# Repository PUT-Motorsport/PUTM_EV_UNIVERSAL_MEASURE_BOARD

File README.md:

# Universal Measurement Board v2.0

---

# Changes

Revision 2.0 has the same functionality as v1.1 but has been reduced in size to meet the 10×10 cm production constraints required by the manufacturer.

# Description

UMB (Universal Measurement Board) is a project designed as multi-channel analog input device to allow various types of electrical measurements.
It provides 8 channels that can be used either as differential or single-ended measurement inputs. All signals are routed through an analog multiplexer, a programmable gain amplifier and an external ADC. Measurements are acquired by a microcontroller and transmitted via an FDCAN interface to a host device for further processing.

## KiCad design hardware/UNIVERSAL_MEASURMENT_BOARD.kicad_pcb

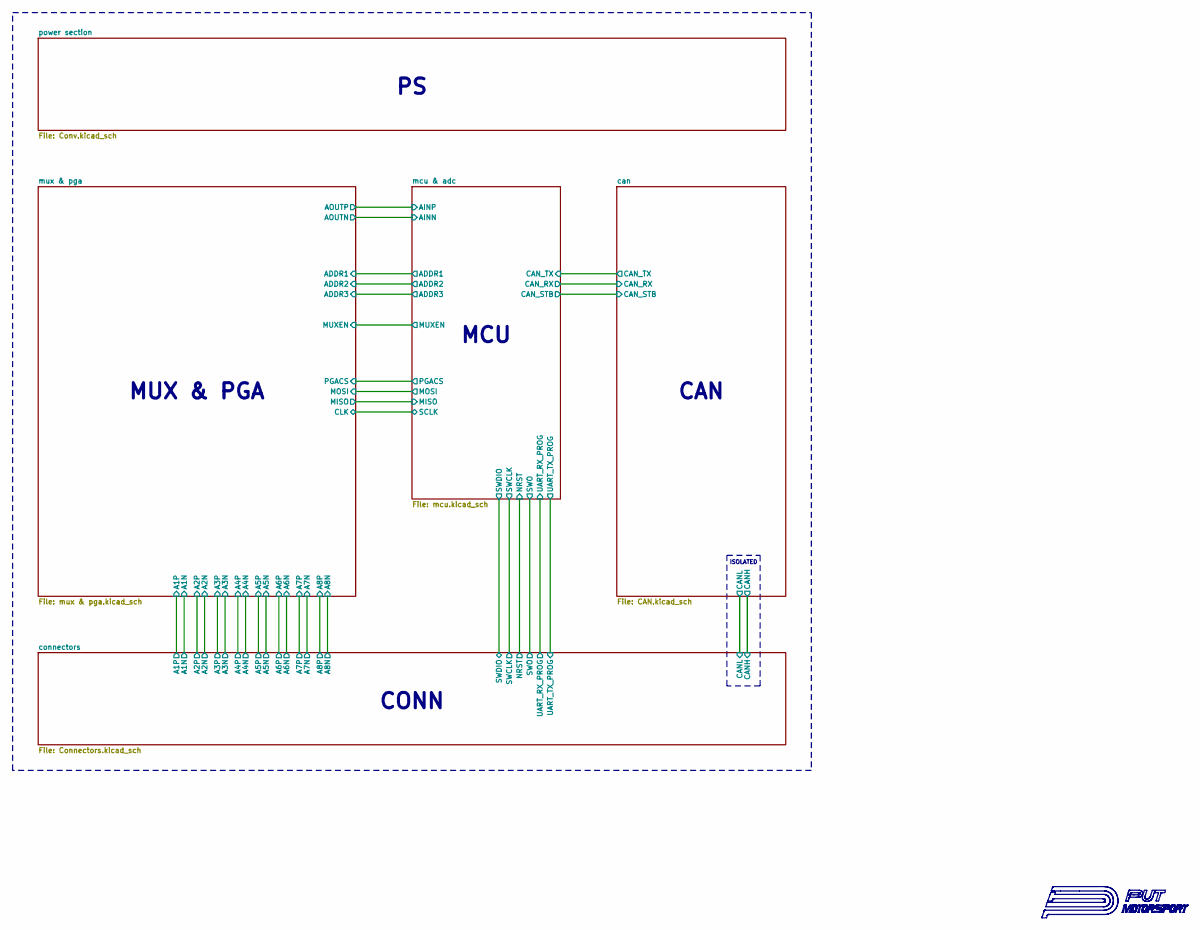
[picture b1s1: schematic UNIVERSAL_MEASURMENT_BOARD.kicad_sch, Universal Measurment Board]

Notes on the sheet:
CAN
CONN
MUX & PGA
MCU
ISOLATED

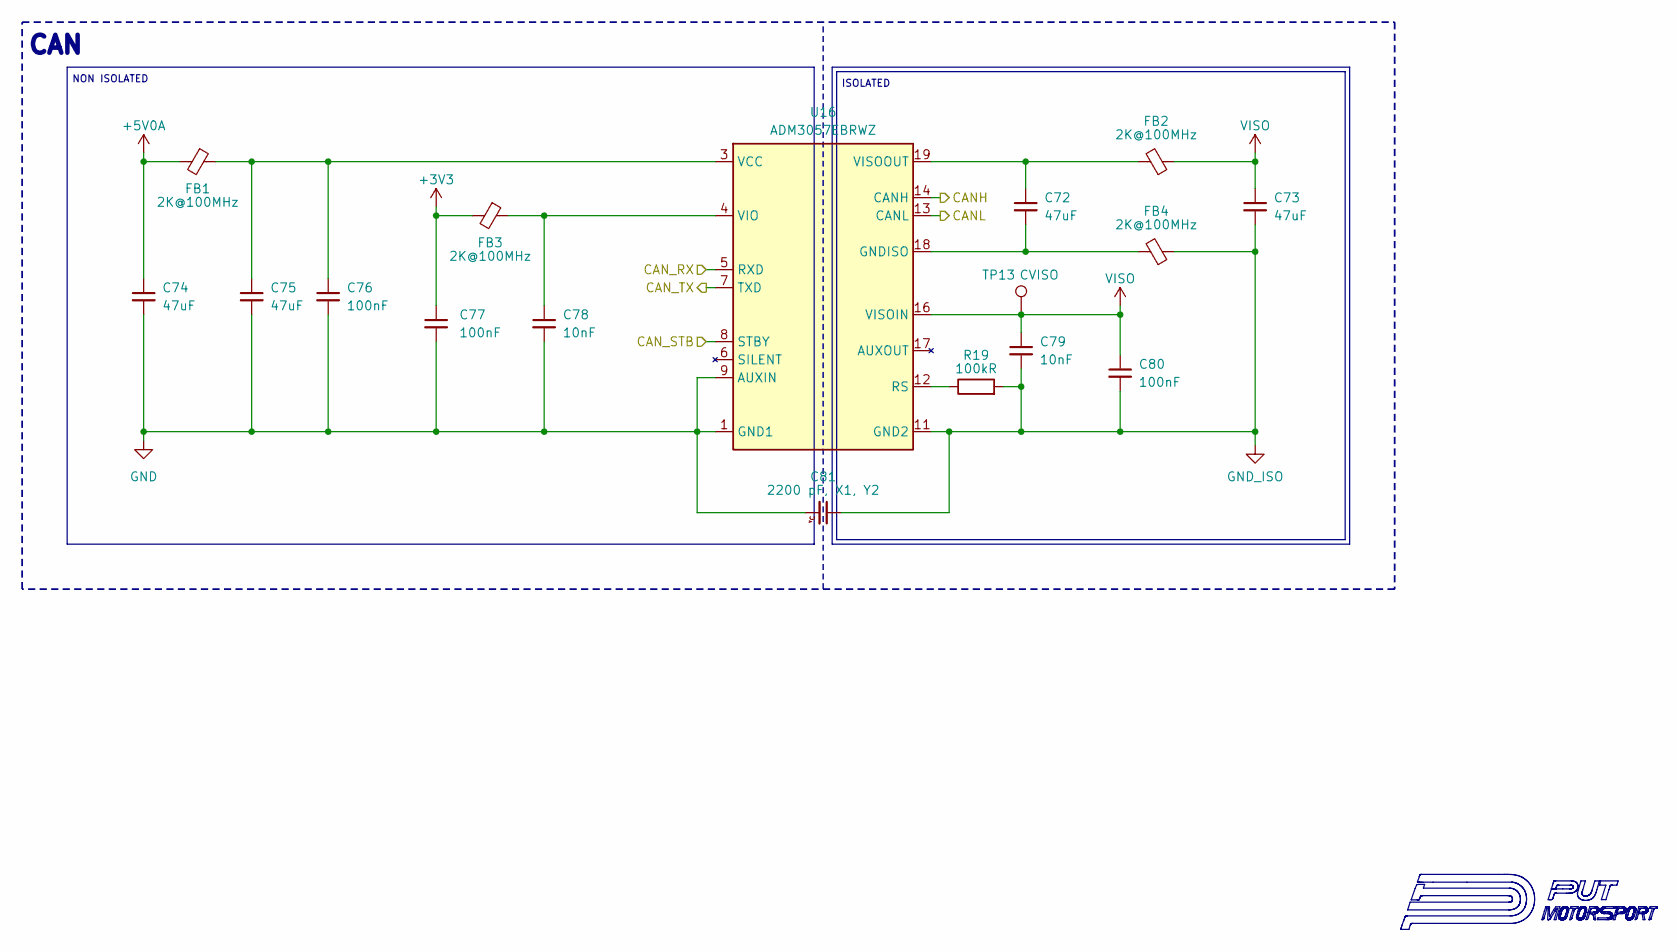
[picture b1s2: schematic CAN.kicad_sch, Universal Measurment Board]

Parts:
C72, C73, C74, C75: 47uF; C_0603_1608Metric
C76, C77, C80: 100nF; C_0603_1608Metric
C78, C79: 10nF; C_0603_1608Metric
C81: 2200 pF, X1, Y2; CAPC5728X280N; Mouser Part Number 791-S252B222K502CT
FB1, FB2, FB3, FB4: 2K@100MHz; L_0805_2012Metric
R19: 100kR; R_0603_1608Metric
TP13: CVISO; TestPoint_Pad_D1.5mm
U16: ADM3057EBRWZ; SOIC127P1032X265-20N; Mouser Part Number 584-ADM3057EBRWZ

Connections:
+3V3: C77.1, FB3.2; also elsewhere on the board
+5V0A: C74.1, FB1.2; also elsewhere on the board
/can/CANH: U16.14 (CANH); also elsewhere on the board
/can/CANL: U16.13 (CANL); also elsewhere on the board
/can/CAN_RX: U16.5 (RXD); also elsewhere on the board
/can/CAN_STB: U16.8 (STBY); also elsewhere on the board
/can/CAN_TX: U16.7 (TXD); also elsewhere on the board
GND: C74.2, C75.2, C76.2, C77.2, C78.2, C81.2, U16.1 (GND1), U16.2 (GND1_2), U16.9 (AUXIN), U16.10 (GND1_3); also elsewhere on the board
GND_ISO: C73.2, C79.2, C80.2, C81.1, FB4.1, R19.2, U16.11 (GND2), U16.15 (GND2_2); also elsewhere on the board
unnamed: C72.2, FB4.2, U16.18 (GNDISO), U16.20 (GNDISO_2)
unnamed: R19.1, U16.12 (RS)
unnamed: C75.1, C76.1, FB1.1, U16.3 (VCC)
unnamed: C78.1, FB3.1, U16.4 (VIO)
unnamed: C72.1, FB2.2, U16.19 (VISOOUT)
VISO: C73.1, C79.1, C80.1, FB2.1, TP13.1, U16.16 (VISOIN)

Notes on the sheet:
CAN
ISOLATED
NON ISOLATED

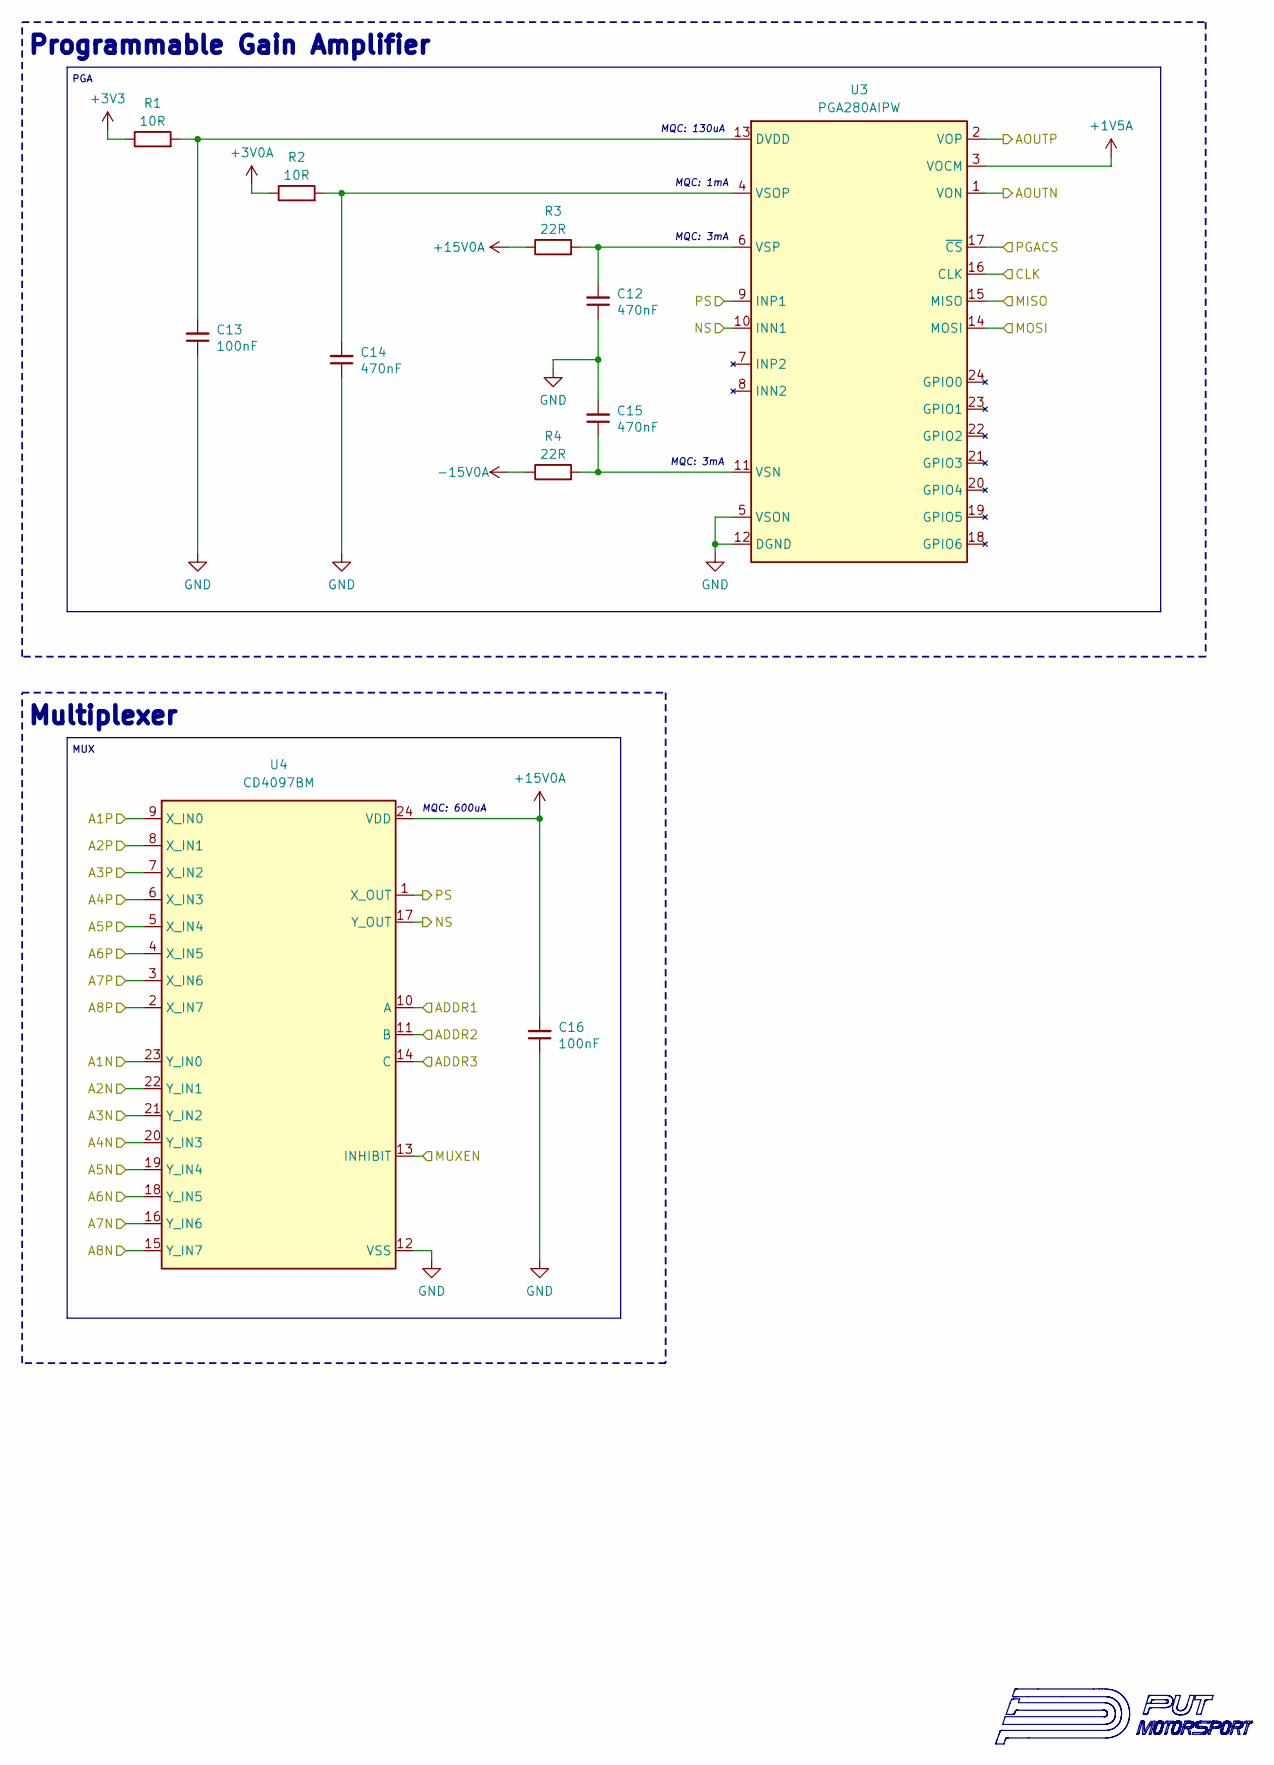
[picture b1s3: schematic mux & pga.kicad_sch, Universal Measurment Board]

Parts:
C12, C14, C15: 470nF; C_0603_1608Metric; Manufacturer_Part_Number CL21A107MQYNNWE; Mouser Part Number 810-C2012X5R1V226MAC
C13, C16: 100nF; C_0603_1608Metric; Manufacturer_Part_Number CL21A107MQYNNWE; Mouser Part Number 810-C2012X5R1V226MAC
R1, R2: 10R; R_0603_1608Metric
R3, R4: 22R; R_0603_1608Metric
U3: PGA280AIPW; SOP65P640X120-24N; Mouser Part Number 595-PGA280AIPW
U4: CD4097BM; SOIC127P1030X265-24N; Mouser Part Number 595-CD4097BM

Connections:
+1V5A: U3.3 (VOCM); also elsewhere on the board
+3V0A: R2.1; also elsewhere on the board
+3V3: R1.1; also elsewhere on the board
+15V0A: C16.2, R3.1, U4.24 (VDD); also elsewhere on the board
-15V0A: R4.1; also elsewhere on the board
/connectors/A1N: U4.23 (Y_IN0); also elsewhere on the board
/connectors/A1P: U4.9 (X_IN0); also elsewhere on the board
/connectors/A2N: U4.22 (Y_IN1); also elsewhere on the board
/connectors/A2P: U4.8 (X_IN1); also elsewhere on the board
/connectors/A3N: U4.21 (Y_IN2); also elsewhere on the board
/connectors/A3P: U4.7 (X_IN2); also elsewhere on the board
/connectors/A4N: U4.20 (Y_IN3); also elsewhere on the board
/connectors/A4P: U4.6 (X_IN3); also elsewhere on the board
/connectors/A5N: U4.19 (Y_IN4); also elsewhere on the board
/connectors/A5P: U4.5 (X_IN4); also elsewhere on the board
/connectors/A6N: U4.18 (Y_IN5); also elsewhere on the board
/connectors/A6P: U4.4 (X_IN5); also elsewhere on the board
/connectors/A7N: U4.16 (Y_IN6); also elsewhere on the board
/connectors/A7P: U4.3 (X_IN6); also elsewhere on the board
/connectors/A8N: U4.15 (Y_IN7); also elsewhere on the board
/connectors/A8P: U4.2 (X_IN7); also elsewhere on the board
/mcu & adc/ADDR1: U4.10 (A); also elsewhere on the board
/mcu & adc/ADDR2: U4.11 (B); also elsewhere on the board
/mcu & adc/ADDR3: U4.14 (C); also elsewhere on the board
/mcu & adc/AINN: U3.1 (VON); also elsewhere on the board
/mcu & adc/AINP: U3.2 (VOP); also elsewhere on the board
/mcu & adc/MISO: U3.15 (MISO); also elsewhere on the board
/mcu & adc/MOSI: U3.14 (MOSI); also elsewhere on the board
/mcu & adc/MUXEN: U4.13 (INHIBIT); also elsewhere on the board
/mcu & adc/PGACS: U3.17 (~CS); also elsewhere on the board
/mcu & adc/SCLK: U3.16 (CLK); also elsewhere on the board
/mux & pga/NS: U3.10 (INN1), U4.17 (Y_OUT)
/mux & pga/PS: U3.9 (INP1), U4.1 (X_OUT)
GND: C12.1, C13.1, C14.1, C15.2, C16.1, U3.5 (VSON), U3.12 (DGND), U4.12 (VSS); also elsewhere on the board
unnamed: C13.2, R1.2, U3.13 (DVDD)
unnamed: C15.1, R4.2, U3.11 (VSN)
unnamed: C14.2, R2.2, U3.4 (VSOP)
unnamed: C12.2, R3.2, U3.6 (VSP)

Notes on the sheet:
MQC: 130uA
Multiplexer
MQC: 1mA
PGA
Programmable Gain Amplifier
MQC: 600uA
MQC: 3mA
MUX

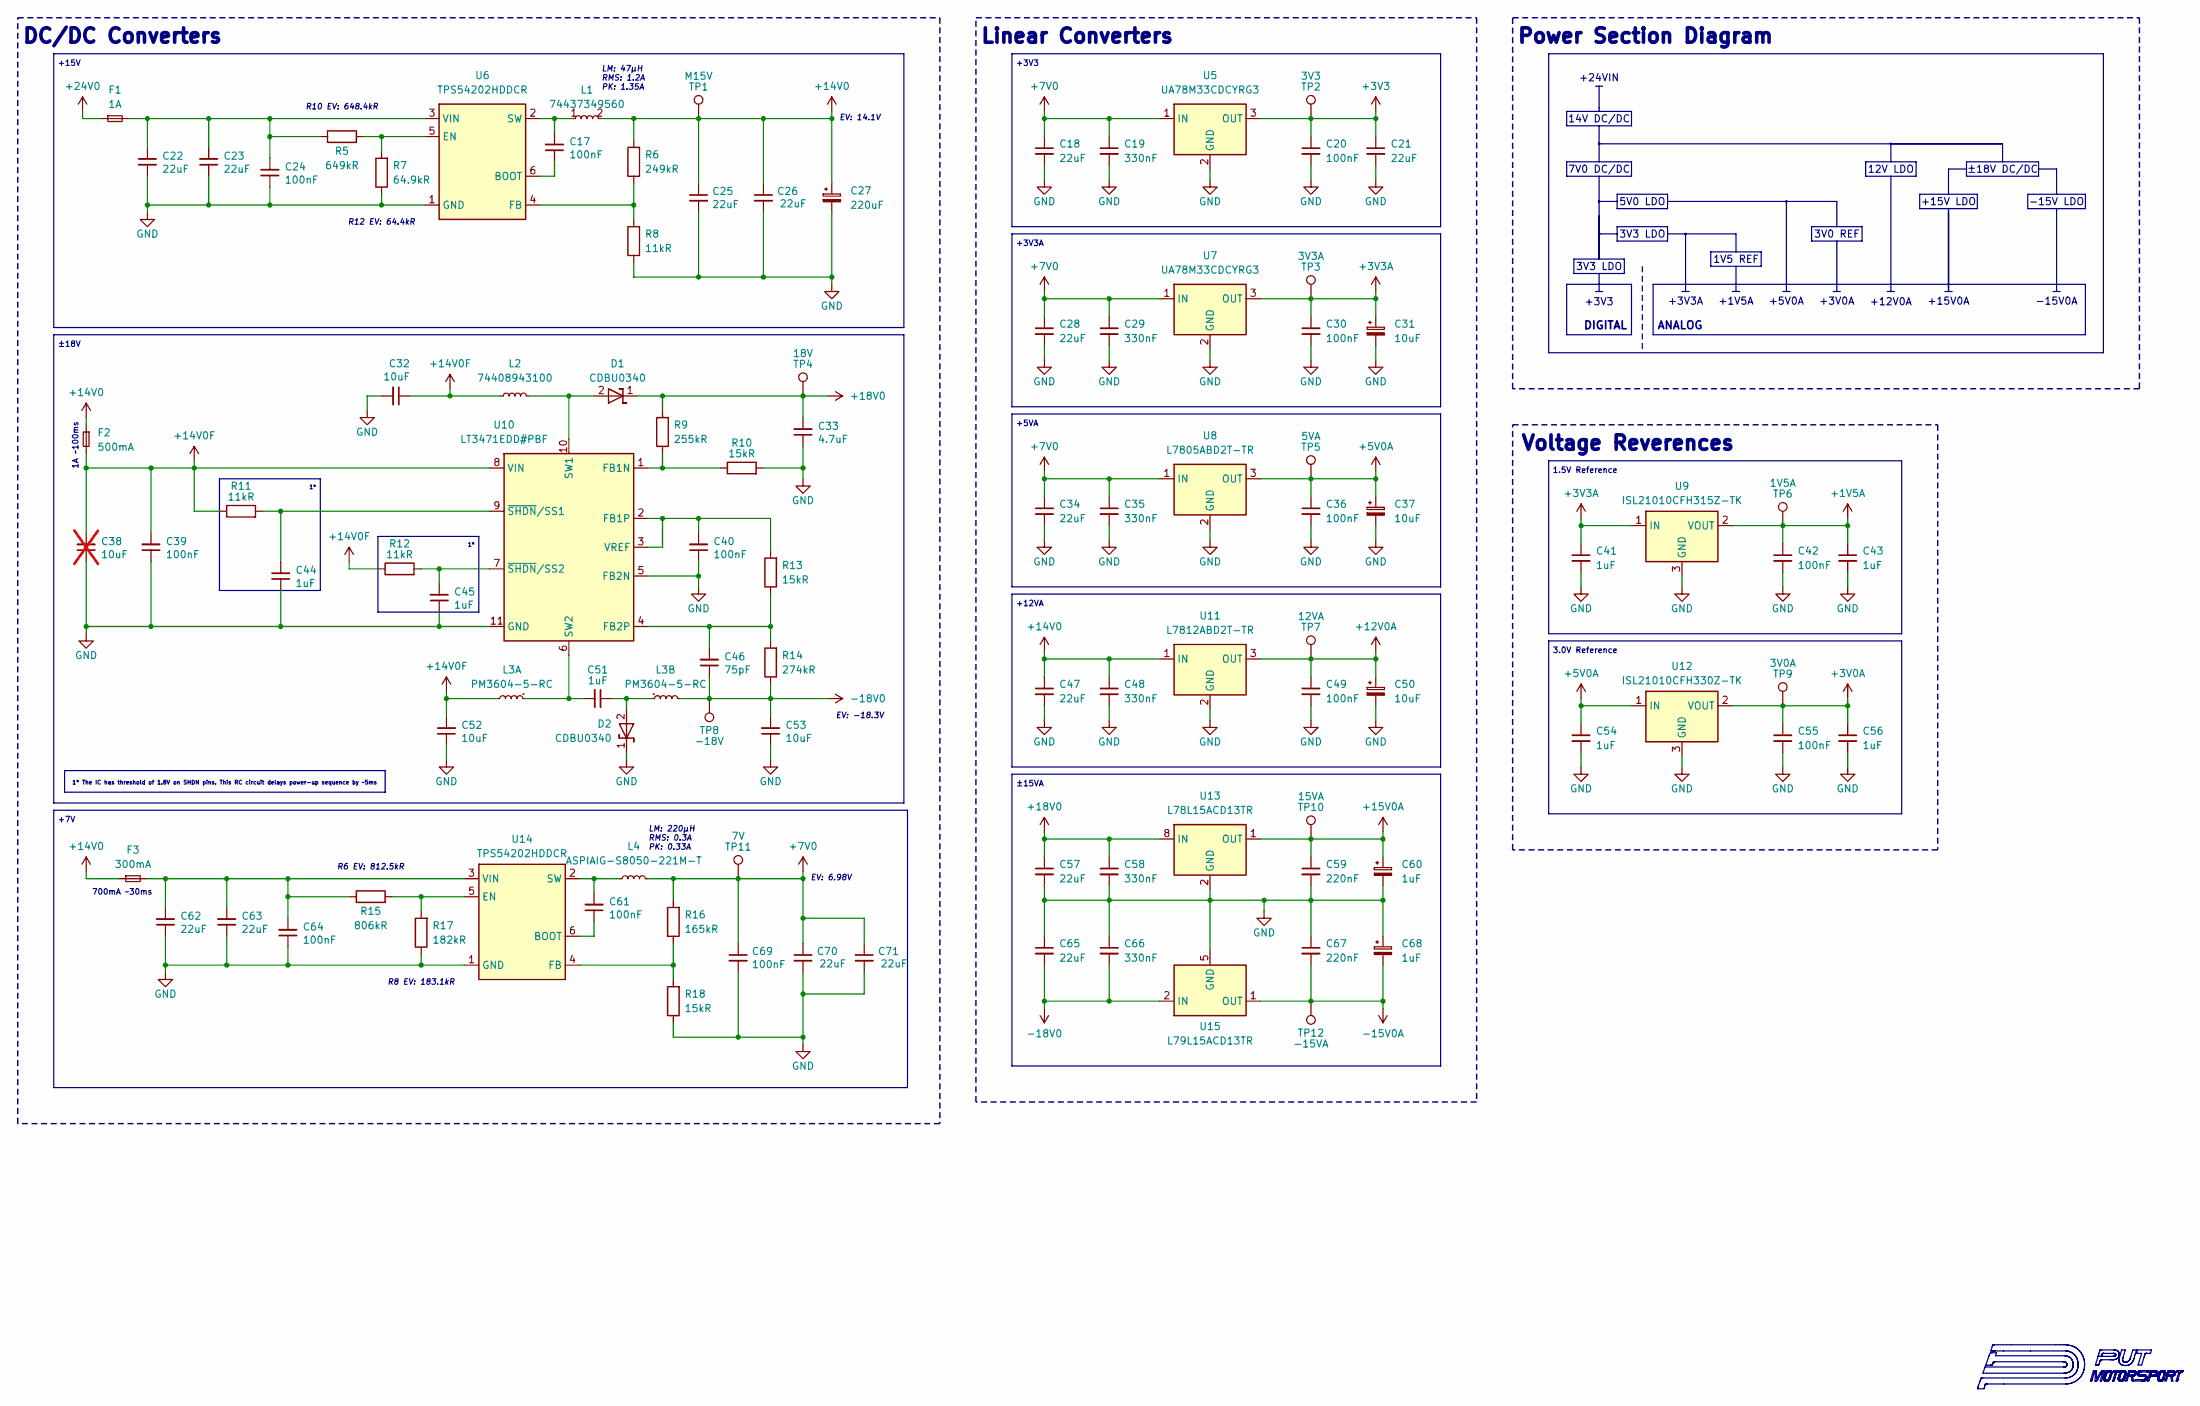
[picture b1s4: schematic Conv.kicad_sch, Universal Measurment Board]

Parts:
C17, C24, C61, C64: 100nF; C_0603_1608Metric; Manufacturer_Part_Number C0603C104J3RACTU; Mouser Part Number --
C18, C21, C28, C34, C47, C57, C62, C63, C65, C70, C71: 22uF; C_0603_1608Metric; Manufacturer_Part_Number CL21A107MQYNNWE; Mouser Part Number 810-C2012X5R1V226MAC
C19, C29, C35, C48, C58, C66: 330nF; C_0603_1608Metric; Manufacturer_Part_Number CL21A107MQYNNWE; Mouser Part Number 810-C2012X5R1V226MAC
C20, C30, C36, C39, C40, C42, C49, C55, C69: 100nF; C_0603_1608Metric; Manufacturer_Part_Number CL21A107MQYNNWE; Mouser Part Number 810-C2012X5R1V226MAC
C22, C23, C25, C26: 22uF; C_0805_2012Metric; Manufacturer_Part_Number CL21A107MQYNNWE; Mouser Part Number 810-C2012X5R1V226MAC
C27: 220uF; CP_Elec_8x10
C31, C37, C50: 10uF; CP_Elec_4x5.8
C32, C52, C53: 10uF; C_0805_2012Metric; Manufacturer_Part_Number CL21A107MQYNNWE; Mouser Part Number 810-C2012X5R1V226MAC
C33: 4.7uF; C_0805_2012Metric; Manufacturer_Part_Number CL21A107MQYNNWE; Mouser Part Number 810-C2012X5R1V226MAC
C38: 10uF; C_0805_2012Metric; Manufacturer_Part_Number CL21A107MQYNNWE; Mouser Part Number 810-C2012X5R1V226MAC; not fitted
C41, C43, C44, C45, C54, C56: 1uF; C_0603_1608Metric; Manufacturer_Part_Number CL21A107MQYNNWE; Mouser Part Number 810-C2012X5R1V226MAC
C46: 75pF; C_0603_1608Metric; Manufacturer_Part_Number CL21A107MQYNNWE; Mouser Part Number 810-C2012X5R1V226MAC
C51: 1uF; C_0805_2012Metric; Manufacturer_Part_Number CL21A107MQYNNWE; Mouser Part Number 810-C2012X5R1V226MAC
C59, C67: 220nF; C_0603_1608Metric; Manufacturer_Part_Number CL21A107MQYNNWE; Mouser Part Number 810-C2012X5R1V226MAC
C60, C68: 1uF; CP_Elec_4x5.4
D1, D2: CDBU0340; D_0603_1608Metric; Mouser Part Number 750-CDBU0340
F1: 1A; F_0805_2012Metric
F2: 500mA; F_0603_1608Metric
F3: 300mA; F_0603_1608Metric
L1: 74437349560; Mouser Part Number 710-74437349560
L2: 74408943100; WE-SPC_48XX78; Mouser Part Number 710-74408943100
L3: PM3604-5-RC; Mouser Part Number 710-74408943100
L4: ASPIAIG-S8050-221M-T; INDPM8080X520N; Mouser Part Number 815-ASPIAIGS8050221T
R5: 649kR; R_0603_1608Metric
R6: 249kR; R_0603_1608Metric
R7: 64.9kR; R_0603_1608Metric
R8, R11, R12: 11kR; R_0603_1608Metric
R9: 255kR; R_0603_1608Metric
R10, R13, R18: 15kR; R_0603_1608Metric
R14: 274kR; R_0603_1608Metric
R15: 806kR; R_0603_1608Metric
R16: 165kR; R_0603_1608Metric
R17: 182kR; R_0603_1608Metric
TP1: M15V; TestPoint_Pad_D1.5mm
TP2: 3V3; TestPoint_Pad_D1.5mm
TP3: 3V3A; TestPoint_Pad_D1.5mm
TP4: 18V; TestPoint_Pad_D1.5mm
TP5: 5VA; TestPoint_Pad_D1.5mm
TP6: 1V5A; TestPoint_Pad_D1.5mm
TP7: 12VA; TestPoint_Pad_D1.5mm
TP8: -18V; TestPoint_Pad_D1.5mm
TP9: 3V0A; TestPoint_Pad_D1.5mm
TP10: 15VA; TestPoint_Pad_D1.5mm
TP11: 7V; TestPoint_Pad_D1.5mm
TP12: -15VA; TestPoint_Pad_D1.5mm
U5, U7: UA78M33CDCYRG3; SOT230P700X180-4N; Mouser Part Number 595-UA78M33CDCYRG3
U6, U14: TPS54202HDDCR; SOT95P280X110-6N; Mouser Part Number 595-TPS54202HDDCR
U8: L7805ABD2T-TR; L7805ABD2TTR; Mouser Part Number 511-L7805ABD2T-TR
U9: ISL21010CFH315Z-TK; SOT95P237X112-3N; Mouser Part Number 968-ISL21010CFH315ZT
U10: LT3471EDD#PBF; SON50P300X300X80-11N-D; Mouser Part Number 584-LT3471EDD#PBF
U11: L7812ABD2T-TR; L7805ABD2TTR; Mouser Part Number 511-L7812ABD2T-TR
U12: ISL21010CFH330Z-TK; SOT95P237X112-3N; Mouser Part Number 968-ISL21010CFH330ZT
U13: L78L15ACD13TR; SOIC127P600X175-8N; Mouser Part Number 511-L78L15ACD-TR
U15: L79L15ACD13TR; SOIC127P600X175-8N; Mouser Part Number 511-L79L15ACD-TR

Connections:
+1V5A: C42.1, C43.1, TP6.1, U9.2 (VOUT); also elsewhere on the board
+3V0A: C55.1, C56.1, TP9.1, U12.2 (VOUT); also elsewhere on the board
+3V3: C20.1, C21.1, TP2.1, U5.3 (OUT); also elsewhere on the board
+3V3A: C30.1, C31.1, C41.1, TP3.1, U7.3 (OUT), U9.1 (IN); also elsewhere on the board
+5V0A: C36.1, C37.1, C54.1, TP5.1, U8.3 (OUT), U12.1 (IN); also elsewhere on the board
+7V0: C18.1, C19.1, C28.1, C29.1, C34.1, C35.1, C69.1, C70.1, C71.1, L4.2, R16.2, TP11.1, U5.1 (IN), U7.1 (IN), U8.1 (IN)
+12V0A: C49.1, C50.1, TP7.1, U11.3 (OUT); also elsewhere on the board
+14V0: C25.1, C26.1, C27.1, C47.1, C48.1, F2.1, F3.1, L1.2, R6.2, TP1.1, U11.1 (IN)
+14V0F: C32.1, C38.2, C39.2, C52.2, F2.2, L2.1, L3.2, R11.1, R12.1, U10.8 (VIN)
+15V0A: C59.1, C60.1, TP10.1, U13.1 (OUT); also elsewhere on the board
+18V0: C33.2, C57.1, C58.1, D1.1 (K), R9.2, TP4.1, U13.8 (IN)
+24V0: F1.1; also elsewhere on the board
-15V0A: C67.2, C68.2, TP12.1, U15.1 (OUT); also elsewhere on the board
-18V0: C46.1, C53.2, C65.2, C66.2, L3.3, R14.1, TP8.1, U15.2 (IN), U15.3 (VIN_2), U15.6 (VIN_3), U15.7 (VIN_4)
GND: C18.2, C19.2, C20.2, C21.2, C22.1, C23.1, C24.1, C25.2, C26.2, C27.2, C28.2, C29.2, C30.2, C31.2, C32.2, C33.1, C34.2, C35.2, C36.2, C37.2, C38.1, C39.1, C40.1, C41.2, C42.2, C43.2, C44.1, C45.1, C47.2, C48.2, C49.2, C50.2, C52.1, C53.1, C54.2, C55.2, C56.2, C57.2, C58.2, C59.2, C60.2, C62.1, C63.1, C64.1, C65.1, C66.1, C67.1, C68.1, C69.2, C70.2, C71.2, D2.1 (K), R7.1, R8.1, R10.2, R17.1, R18.1, U5.2 (GND), U5.4 (GND), U6.1 (GND), U7.2 (GND), U7.4 (GND), U8.2 (GND), U9.3 (GND), U10.5 (FB2N), U10.11 (GND), U11.2 (GND), U12.3 (GND), U13.2 (GND), U13.3 (GND_2), U13.6 (GND_3), U13.7 (GND_4), U14.1 (GND), U15.5 (GND); also elsewhere on the board
unnamed: D1.2 (A), L2.2, U10.10 (SW1)
unnamed: C51.1, D2.2 (A), L3.4
unnamed: C17.1, U6.6 (BOOT)
unnamed: R5.2, R7.2, U6.5 (EN)
unnamed: R6.1, R8.2, U6.4 (FB)
unnamed: C17.2, L1.1, U6.2 (SW)
unnamed: C22.2, C23.2, C24.2, F1.2, R5.1, U6.3 (VIN)
unnamed: R9.1, R10.1, U10.1 (FB1N)
unnamed: C40.2, R13.2, U10.2 (FB1P), U10.3 (VREF)
unnamed: C46.2, R13.1, R14.2, U10.4 (FB2P)
unnamed: C51.2, L3.1, U10.6 (SW2)
unnamed: C44.2, R11.2, U10.9 (~SHDN/SS1)
unnamed: C45.2, R12.2, U10.7 (~SHDN/SS2)
unnamed: C61.1, U14.6 (BOOT)
unnamed: R15.2, R17.2, U14.5 (EN)
unnamed: R16.1, R18.2, U14.4 (FB)
unnamed: C61.2, L4.1, U14.2 (SW)
unnamed: C62.2, C63.2, C64.2, F3.2, R15.1, U14.3 (VIN)

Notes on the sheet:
Linear Converters
LM: 47µH RMS: 1.2A PK: 1.35A
700mA ~30ms
+15V LDO
3V0 REF
±18V
+3V3
+3V0A
3V3 LDO
+7V
+3V3A
+1V5A
1* The IC has threshold of 1.8V on SHDN pins. This RC circuit delays power-up sequence by ~5ms
5V0 LDO
±15VA
12V LDO
+15V
EV: -18.3V
ANALOG
Power Section Diagram
EV: 14.1V
+5VA
+12V0A
DIGITAL
DC/DC Converters
14V DC/DC
R6 EV: 812.5kR
-15V LDO
+12VA
R12 EV: 64.4kR
±18V DC/DC
1V5 REF
R10 EV: 648.4kR
1.5V Reference
+24VIN
3.0V Reference
LM: 220µH RMS: 0.3A PK: 0.33A
EV: 6.98V
-15V0A
R8 EV: 183.1kR

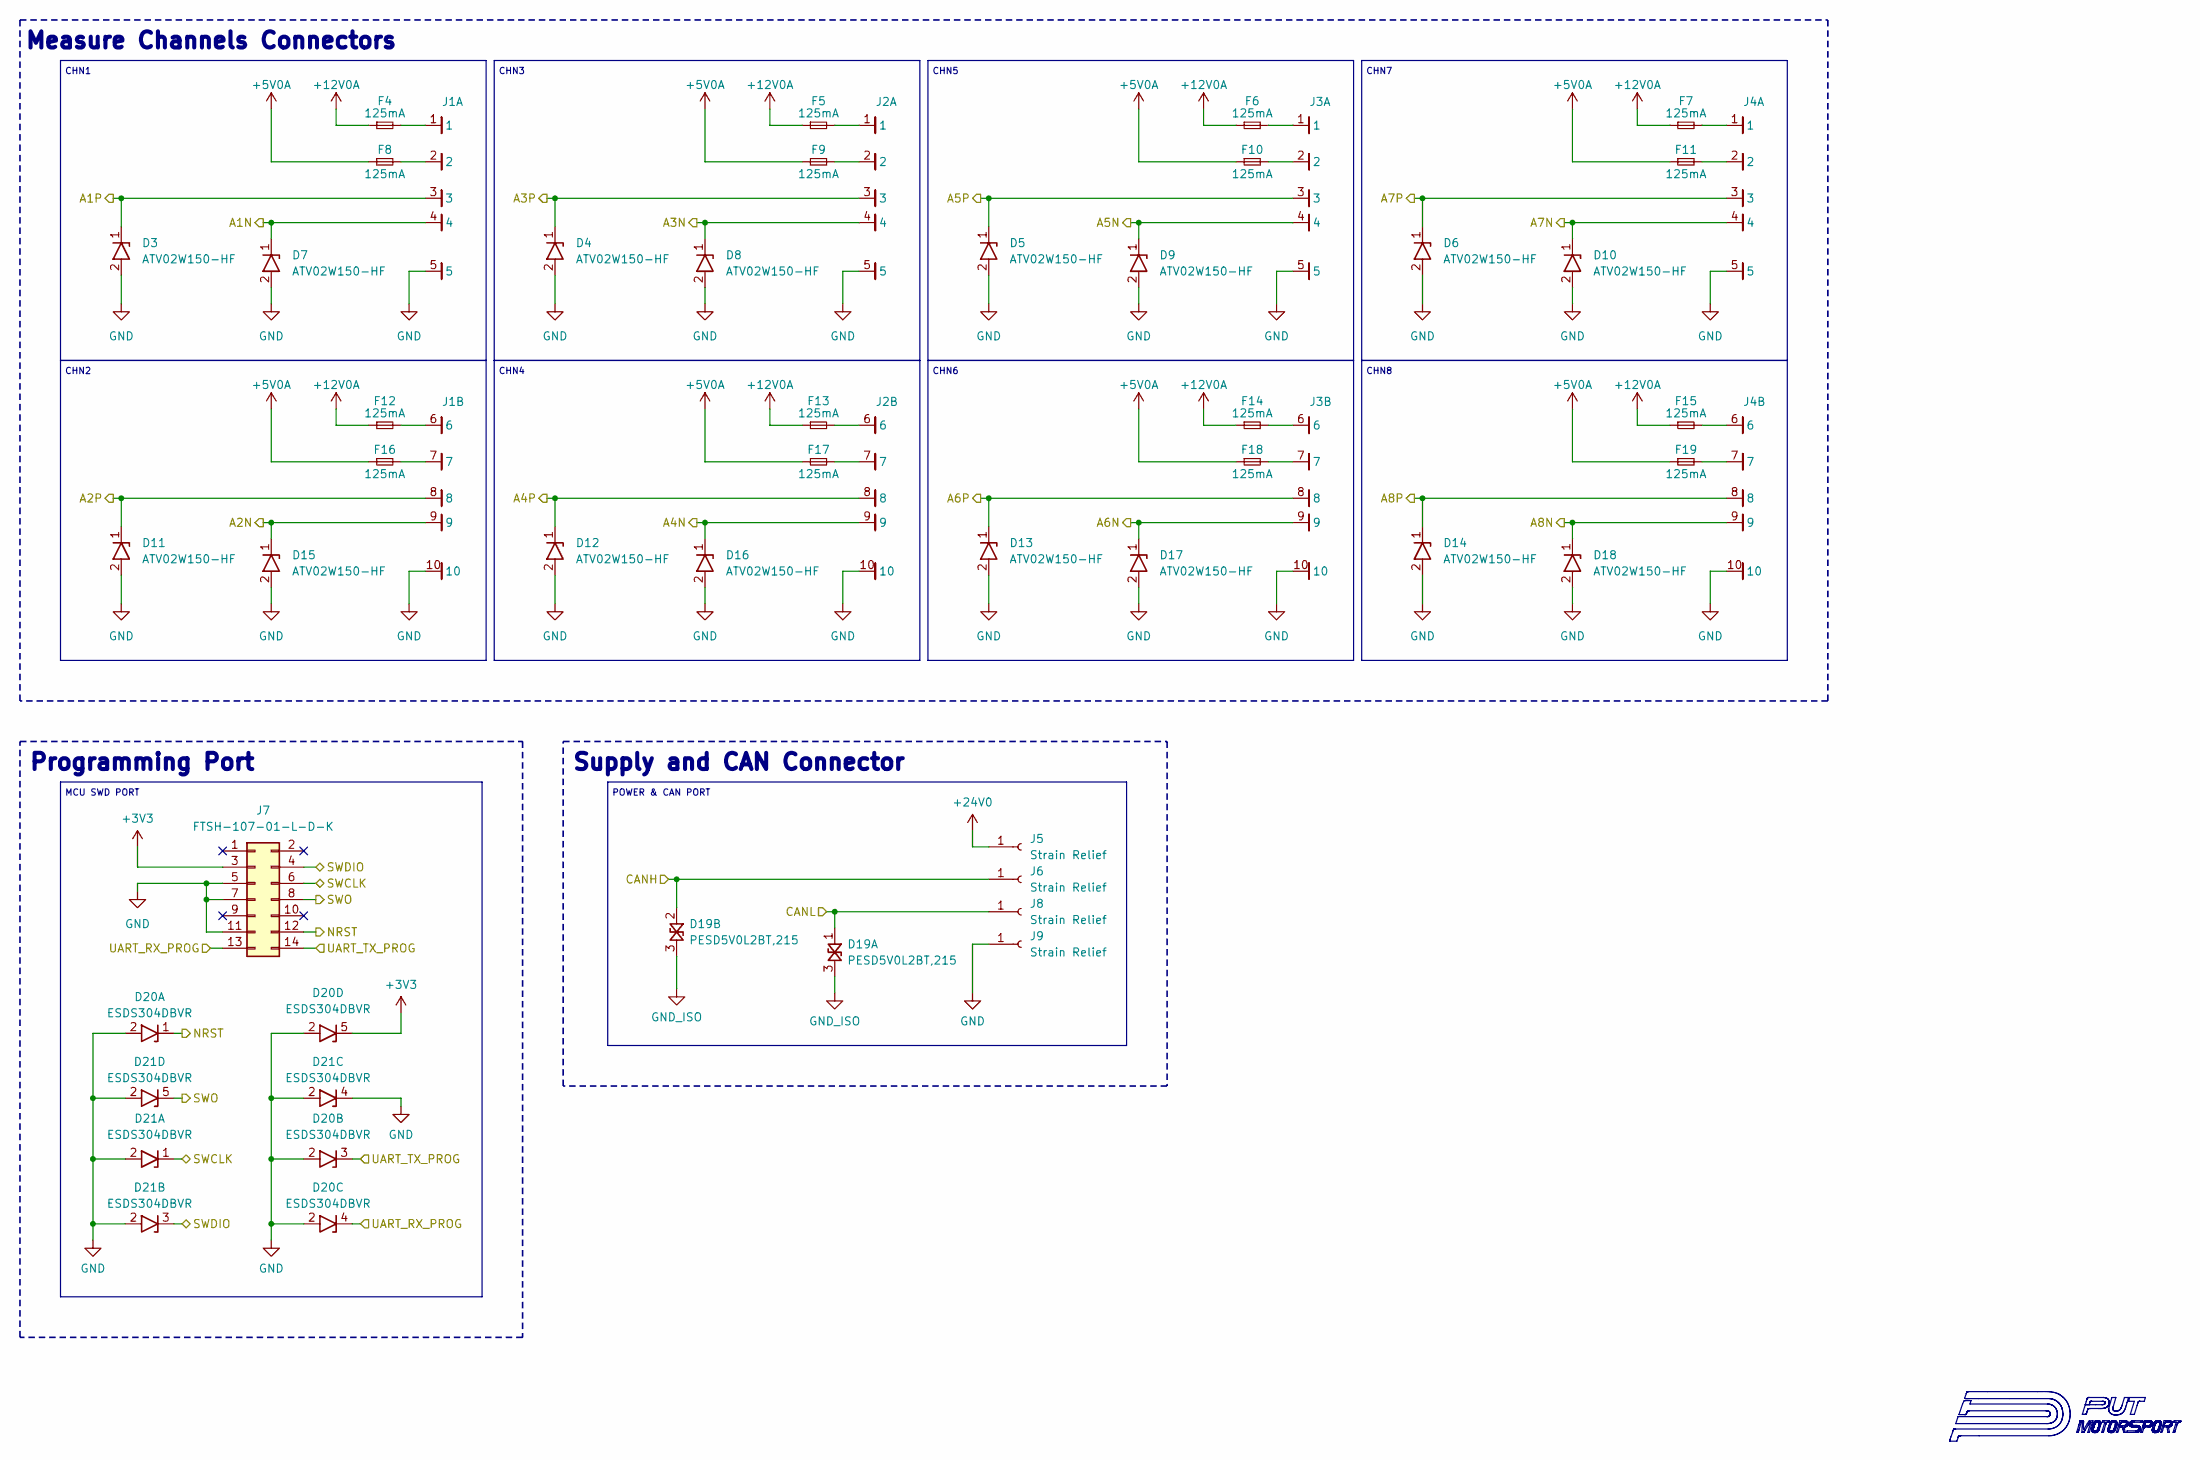
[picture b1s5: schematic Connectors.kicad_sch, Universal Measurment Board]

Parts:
D3, D4, D5, D6, D7, D8, D9, D10, D11, D12, D13, D14, D15, D16, D17, D18: ATV02W150-HF; SODFL3718X130N; Mouser Part Number 750-ATV02W150-HF
D19: PESD5V0L2BT,215; SOT95P230X110-3N; Mouser Part Number 771-PESD5V0L2BT-T/R
D20, D21: ESDS304DBVR; SOT95P280X145-5N; Mouser Part Number 595-ESDS304DBVR
F4, F5, F6, F7, F8, F9, F10, F11, F12, F13, F14, F15, F16, F17, F18, F19: 125mA; F_1206_3216Metric
J1, J2, J3, J4: 2606-1110_010-000; 26011110; Manufacturer_Part_Number 2606-1110/010-000
J5, J6, J8, J9: Strain Relief; SolderPoint
J7: FTSH-107-01-L-D-K; FTSH-107-XX-YYY-D-K; Mouser Part Number 200-FTSH10701LDK

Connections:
+3V3: D20.5, J7.3; also elsewhere on the board
+5V0A: F8.1, F9.1, F10.1, F11.1, F16.1, F17.1, F18.1, F19.1; also elsewhere on the board
+12V0A: F4.1, F5.1, F6.1, F7.1, F12.1, F13.1, F14.1, F15.1; also elsewhere on the board
+24V0: J5.1 (Pin_1_1); also elsewhere on the board
/can/CANH: D19.2, J6.1 (Pin_1_1); also elsewhere on the board
/can/CANL: D19.1, J8.1 (Pin_1_1); also elsewhere on the board
/connectors/A1N: D7.1, J1.4; also elsewhere on the board
/connectors/A1P: D3.1, J1.3; also elsewhere on the board
/connectors/A2N: D15.1, J1.9; also elsewhere on the board
/connectors/A2P: D11.1, J1.8; also elsewhere on the board
/connectors/A3N: D8.1, J2.4; also elsewhere on the board
/connectors/A3P: D4.1, J2.3; also elsewhere on the board
/connectors/A4N: D16.1, J2.9; also elsewhere on the board
/connectors/A4P: D12.1, J2.8; also elsewhere on the board
/connectors/A5N: D9.1, J3.4; also elsewhere on the board
/connectors/A5P: D5.1, J3.3; also elsewhere on the board
/connectors/A6N: D17.1, J3.9; also elsewhere on the board
/connectors/A6P: D13.1, J3.8; also elsewhere on the board
/connectors/A7N: D10.1, J4.4; also elsewhere on the board
/connectors/A7P: D6.1, J4.3; also elsewhere on the board
/connectors/A8N: D18.1, J4.9; also elsewhere on the board
/connectors/A8P: D14.1, J4.8; also elsewhere on the board
/connectors/NRST: D20.1, J7.12; also elsewhere on the board
/connectors/SWCLK: D21.1, J7.6; also elsewhere on the board
/connectors/SWDIO: D21.3, J7.4; also elsewhere on the board
/connectors/SWO: D21.5, J7.8; also elsewhere on the board
/connectors/UART_RX_PROG: D20.4, J7.13; also elsewhere on the board
/connectors/UART_TX_PROG: D20.3, J7.14; also elsewhere on the board
GND: D3.2, D4.2, D5.2, D6.2, D7.2, D8.2, D9.2, D10.2, D11.2, D12.2, D13.2, D14.2, D15.2, D16.2, D17.2, D18.2, D20.2, D21.2, D21.4, J1.5, J1.10, J2.5, J2.10, J3.5, J3.10, J4.5, J4.10, J7.5, J7.7, J7.11, J9.1 (Pin_1_1); also elsewhere on the board
GND_ISO: D19.3; also elsewhere on the board
unnamed: F4.2, J1.1
unnamed: F5.2, J2.1
unnamed: F6.2, J3.1
unnamed: F7.2, J4.1
unnamed: F8.2, J1.2
unnamed: F9.2, J2.2
unnamed: F10.2, J3.2
unnamed: F11.2, J4.2
unnamed: F12.2, J1.6
unnamed: F13.2, J2.6
unnamed: F14.2, J3.6
unnamed: F15.2, J4.6
unnamed: F16.2, J1.7
unnamed: F17.2, J2.7
unnamed: F18.2, J3.7
unnamed: F19.2, J4.7

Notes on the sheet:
MCU SWD PORT
Supply and CAN Connector
CHN3
CHN1
CHN6
CHN7
CHN2
POWER & CAN PORT
CHN5
Measure Channels Connectors
Programming Port
CHN8
CHN4
